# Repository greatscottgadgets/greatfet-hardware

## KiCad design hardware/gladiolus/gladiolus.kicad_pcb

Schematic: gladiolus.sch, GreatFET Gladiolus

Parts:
C1, C4: C; 0603
C2, C10, C26: 15pF; 0402; Part Number GRM1555C1H150GA01D
C3, C5, C6, C7, C11, C12, C13, C17, C18, C19, C20, C21, C22, C23, C24, C25, C27: 100nF; 0603; Part Number GRM188R71C104KA01D
C8: 10uF; 0805; Part Number GRM21BR61A106KE19L
C9: 100pF; 0402; Part Number GRM1555C1H101GA01D
C14: 130pF; 0402; Part Number GRM1555C1H131GA01D
C15: 82pF; 0402; Part Number GRM1555C1H820GA01D
C16: 24pF; 0402; Part Number GRM1555C1H240GA01D
D1: PHOTODIODE; LED-3MM; Part Number PD204-6B
D2: PHOTODIODE; VBPW34FASR; Part Number VBPW34FASR
D3: LED; LED-5MM; Part Number TSHF5210
FB1: FILTER; 0805; Part Number BLM21PG221SN1D
J1: NEIGHBOR1; HEADER-2x20; Part Number SSQ-120-23-G-D
J2: NEIGHBOR2; HEADER-2x20; Part Number SSQ-120-23-G-D
J7: BONUS_ROW; HEADER-1x20; Part Number SSQ-120-23-G-S
L1, L2, L5, L6, L7, L8: 2.2uH; 0402; Part Number MLF1005G2R2JT000
L3, L4: 1.5uH; 0402; Part Number MLF1005G1R5KT000
L9, L10: 1uH; 0402; Part Number MLF1005G1R0JT000
MH1, MH2, MH3, MH4: MOUNTING_HOLE; HOLE126MIL-COPPER
P1: CONN_01X05; HEADER-1x5; Part Number PPTC051LFBN-RC
Q1: Q_NPN_BEC; SOT23-3; Part Number BSV52
R1, R2, R3, R4, R9, R19, R20, R21, R22, R23, R26, R29, R31, R38, R39, R40, R41, R42, R43, R44, R45, R67, R72, R74: 0; 0603; Part Number RC0603JR-070RL
R5, R11, R12, R13, R14, R37, R56, R65, R68: R; 0603
R6: 100k; 0402; Part Number RC0402FR-07100KL
R7: 3.24k; 0603; Part Number RC0603FR-073K24L
R8: 1.74k; 0603; Part Number RC0603FR-071K74L
R10, R27, R36, R55, R58, R59, R60, R61, R62, R63: 10k; 0603; Part Number ERJ-3GEYJ103V
R15, R16, R32, R33: 0; 0402; Part Number RC0402JR-070RL
R17, R18, R34, R35: R; 0402
R24, R25, R73: 1k; 0603; Part Number RC0603JR-071KL
R28, R46, R47, R48, R49, R50, R51, R52, R53, R54: 39; 0603; Part Number RC0603JR-0739RL
R30: 75; 0603; Part Number RC0603FR-0775RL
R57: 20k; 0603; Part Number RC0603JR-0720KL
R64, R66, R69: 249; 0603; Part Number 311-249HR
R70: 1.80k; 0603; Part Number RC0603FR-071K8L
R71: 953; 0603; Part Number RC0603FR-07953RL
R75: 12k; 0603; Part Number RC0603JR-0712KL
RV1, RV2, RV3: POT; 3306F; Part Number 3306F-1-103
U1: THS4520RGT; QFN16-3; Part Number THS4520RGT
U2: AD8330ARQZ; TSSOP16; Part Number AD8330ARQZ
U3: AD9283; SSOP20; Part Number AD9283BRSZ-50
U4: AD9704; QFN32-5; Part Number AD9704BCPZ
U5: LMH6643; VSSOP8; Part Number LMH6643MM

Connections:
/ADC0_0: J2.5, R21.2
/ADC0_2: J7.5
/ADC0_5: J7.4
/ADCCLK: R37.1, R46.1, U3.10 (ENCODE)
/CLK0: J1.11
/CLK2: J2.12
/D0: R38.2, U3.20 (D0)
/D1: R39.2, U3.19 (D1)
/D2: R40.2, U3.18 (D2)
/D3: R41.2, U3.17 (D3)
/D4: R42.2, U3.14 (D4)
/D5: R43.2, U3.13 (D5)
/D6: R44.2, U3.12 (D6)
/D7: R45.2, U3.11 (D7)
/DACCLK: R54.1, R56.1, U4.12
/I2C0_SCL: J2.40
/I2C0_SDA: J2.39
/P0_0: J1.4, R38.1
/P0_1: J1.6, R39.1
/P1_0: J1.7, R45.1
/P1_1: J1.10
/P1_2: J1.12
/P1_3: J1.40
/P1_4: J1.39
/P1_5: J1.13, R24.2
/P1_6: J1.16, R54.2
/P1_7: J1.15, R53.2
/P1_8: J1.18, R52.2
/P1_9: J1.17, R51.2
/P1_10: J1.20, R50.2
/P1_11: J1.22, R49.2
/P1_12: J1.21, R48.2
/P1_13: J1.26, R47.2
/P1_14: J1.25, R28.2
/P1_15: J1.28, R40.1
/P1_16: J1.30, R41.1
/P1_17: J1.32
/P1_18: J1.31
/P1_19: J1.38
/P1_20: J1.37
/P2_0: J1.35
/P2_1: J2.35
/P2_2: J2.33, R44.1
/P2_3: J2.20, R36.1, U3.1 (PWRDWN)
/P2_4: J2.19
/P2_5: J2.18, R9.2, R10.2, R19.1
/P2_6: J2.15
/P2_7: J2.14
/P2_8: J2.13
/P2_9: J7.6
/P2_10: J7.14
/P2_11: J7.13
/P2_12: J7.7
/P2_13: J7.8
/P3_0: J2.26
/P3_1: J2.24
/P3_2: J2.22
/P3_3: J2.32
/P3_4: J2.28
/P3_5: J2.37
/P3_6: J2.38
/P3_7: J2.30
/P4_0: J2.4
/P4_2: J2.8
/P4_3: J2.9, R29.2
/P4_4: J2.7, R22.2
/P4_5: J2.6
/P4_6: J2.10
/P4_7: J2.11
/P4_8: J2.3, R26.2
/P4_9: J1.3
/P4_10: J1.5
/P5_0: J1.8, R55.2, U4.25
/P5_1: J1.9
/P5_2: J1.14, R58.2, R59.1, U4.15
/P5_3: J1.19, R60.2, R61.1, U4.16
/P5_4: J1.24
/P5_5: J1.23, R62.2, R63.1, U4.17
/P5_6: J1.27, R25.2
/P5_7: J1.29
/P6_0: J1.36
/P6_1: J7.18
/P6_2: J7.17
/P6_3: J2.36, R42.1
/P6_4: J7.2
/P6_5: J7.3
/P6_6: J2.34, R43.1
/P6_7: J2.31
/P6_8: J2.29
/P6_9: J7.16
/P6_10: J7.15
/P7_0: J2.27
/P7_1: J2.25
/P7_2: J2.23
/P7_7: J2.16
/P9_5: J1.33
/P9_6: J1.34, R46.2
/PF_4: J2.21
/RESET: J7.11
/RTC_ALARM: J7.9
/RXIN: C2.2, D1.2 (A), D2.2 (A), P1.5, R5.1, R6.2, U1.11 (VIN+)
/TXOUT: D3.1 (K), P1.1, Q1.3 (C)
/VBAT: J7.12
/VBUS: J2.2, R3.2
/WAKEUP0: J2.17
GND: C1.2, C3.2, C5.2, C6.2, C7.2, C8.2, C11.2, C12.2, C13.2, C17.1, C18.1, C19.1, C20.1, C21.2, C22.2, C23.2, C24.1, C25.2, C27.2, J1.1, J2.1, J7.1, J7.10, J7.19, MH1.1, MH2.1, MH3.1, MH4.1, P1.2, P1.4, R4.2, R8.1, R10.1, R14.2, R17.1, R18.2, R20.2, R27.2, R30.2, R34.1, R35.2, R37.2, R56.2, R57.1, R59.2, R61.2, R63.2, R64.2, R66.2, R70.2, RV1.1, RV2.1, RV3.1, U1.0 (GND), U1.13 (VS-), U1.14 (VS-), U1.15 (VS-), U1.16 (VS-), U2.8 (CMGN), U2.9 (COMM), U2.11 (CMOP), U3.4 (GND), U3.9 (GND), U3.16 (GND), U4.0, U4.10, U4.14, U4.19, U4.22, U4.26, U5.4
unnamed: C1.1, D1.1 (K), D2.1 (K), R1.2, R2.1, R3.1, R4.1
unnamed: C2.1, L1.2, R6.1, U1.10 (VOUT-)
unnamed: C3.1, C4.2, R1.1, R7.1, R8.2, R11.1, R12.1, RV1.2, U1.2 (VIN-)
unnamed: C4.1, L2.2, R11.2, U1.3 (VOUT+)
unnamed: C5.1, R5.2, U1.9 (CM)
unnamed: C7.1, R12.2, R13.2, R14.1, U1.4 (CM)
unnamed: C9.1, L1.1, L3.2
unnamed: C9.2, L2.1, L4.2
unnamed: C10.1, L3.1, R15.1
unnamed: C10.2, L4.1, R16.1
unnamed: C13.1, R31.1, U2.15 (CNTR)
unnamed: C14.1, L5.1, L7.2
unnamed: C14.2, L6.1, L8.2
unnamed: C15.1, L7.1, L9.2
unnamed: C15.2, L8.1, L10.2
unnamed: C16.1, L9.1, R32.1
unnamed: C16.2, L10.1, R33.1
unnamed: C18.2, R31.2, U3.2 (VREFOUT), U3.3 (VREFIN)
unnamed: C24.2, R67.1, R68.2, U4.23
unnamed: C25.1, R24.1, R25.1, R27.1, R65.2, R67.2, U5.3
unnamed: C26.1, R68.1, R69.1, R70.1, R71.1, U5.2
unnamed: C26.2, R71.2, R72.1, U5.1
unnamed: FB1.2, J1.2
unnamed: L5.2, U2.13 (OPHI)
unnamed: L6.2, U2.12 (OPLO)
unnamed: Q1.1 (B), R73.1
unnamed: Q1.2 (E), R30.1, R74.2
unnamed: R9.1, U1.12 (!PD)
unnamed: R15.2, R17.2, U2.4 (INHI)
unnamed: R16.2, R18.1, U2.5 (INLO)
unnamed: R19.2, U2.2 (ENBL)
unnamed: R20.1, U2.1 (OFST)
unnamed: R21.1, R22.1, RV2.2, U2.7 (VDBS)
unnamed: R23.1, R26.1, U2.6 (MODE)
unnamed: R28.1, U4.27
unnamed: R29.1, RV3.2, U2.10 (VMAG)
unnamed: R32.2, R34.2, U3.6 (AIN-)
unnamed: R33.2, R35.1, U3.7 (AIN+)
unnamed: R47.1, U4.28
unnamed: R48.1, U4.29
unnamed: R49.1, U4.30
unnamed: R50.1, U4.31
unnamed: R51.1, U4.32
unnamed: R52.1, U4.1
unnamed: R53.1, U4.2
unnamed: R57.2, U4.24
unnamed: R72.2, U5.5
unnamed: R73.2, U5.7
unnamed: R74.1, U5.6
unnamed: R75.1, RV2.3
VCC: C6.1, C8.1, C11.1, C12.1, C17.2, C19.2, C20.2, C21.1, C22.1, C23.1, C27.1, D3.2 (A), FB1.1, P1.3, R2.2, R7.2, R13.1, R23.2, R36.2, R55.1, R58.1, R60.1, R62.1, R75.2, RV1.3, RV3.3, U1.5 (VS+), U1.6 (VS+), U1.7 (VS+), U1.8 (VS+), U2.3 (VPSI), U2.14 (VPSO), U2.16 (VPOS), U3.5 (VD), U3.8 (VD), U3.15 (VDD), U4.3, U4.11, U4.18, U5.8

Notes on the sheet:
MISO
MOSI
SCK
SSEL
ISP
DFU
BOOT
10 MHz LPF
SGPIO0
SGPIO1
SGPIO2
SGPIO3
SGPIO4
SGPIO5
SGPIO6
SGPIO7
SGPIO8
P1 blocks direct light from TX to RX
GPIO1[0]
GPIO1[1]
GPIO1[2]
GPIO1[3]
GPIO1[4]
GPIO1[5]
GPIO1[6]
GPIO1[7]
GPIO1[9]
Default configuration: pin mode unsigned binary single-ended clock
GPIO1[8]
GPIO2[15]
GPIO2[12]
GPIO2[14]
GPIO2[11]
GPIO2[9]

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
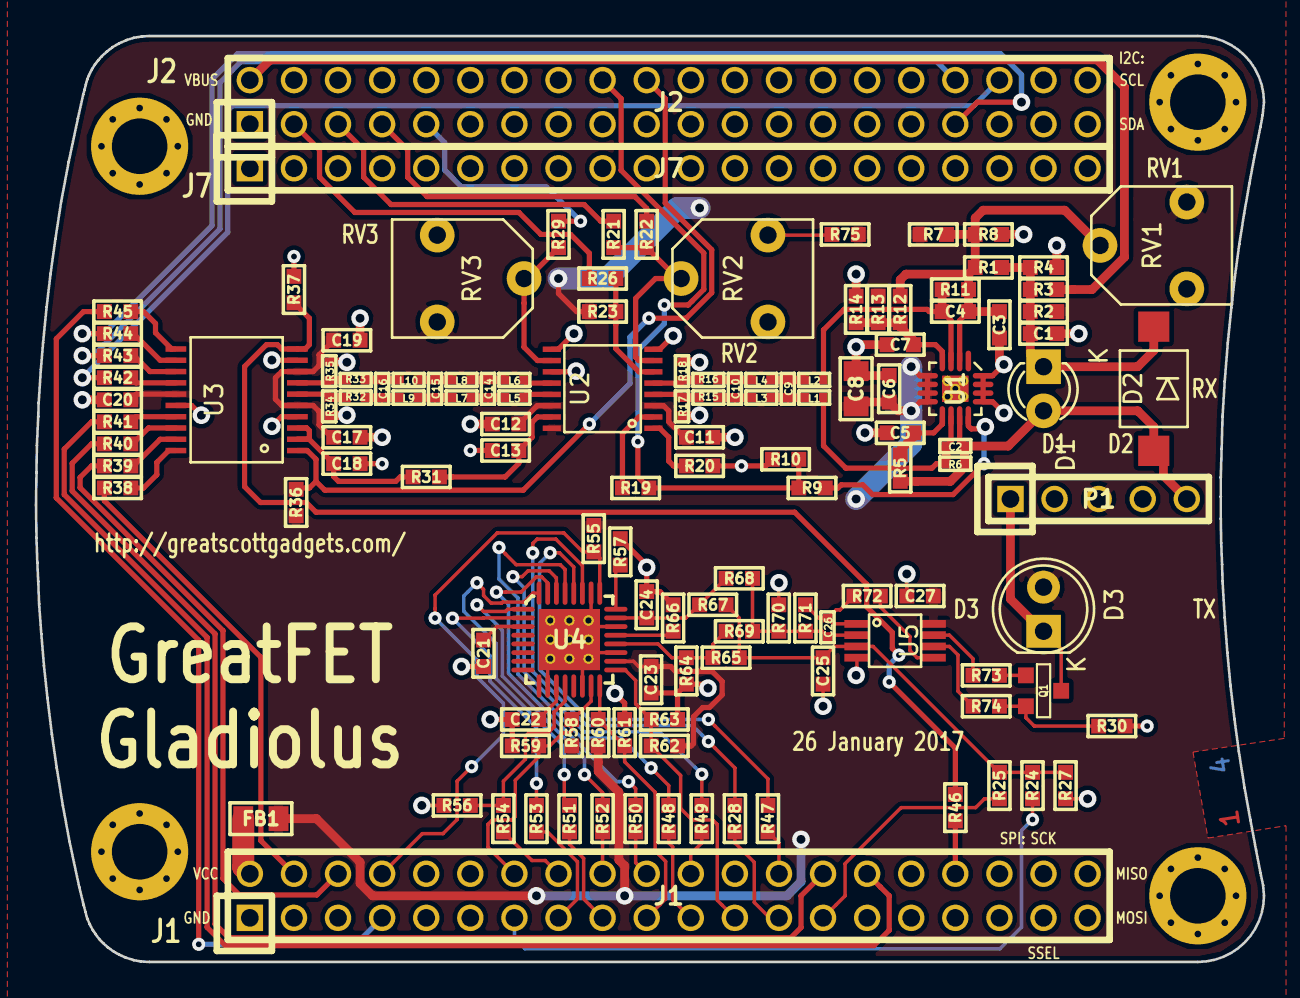
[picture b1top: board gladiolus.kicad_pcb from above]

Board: 4 copper layers, 70.7 x 53.3 mm, 133 parts (0 on the bottom side), 97 nets.

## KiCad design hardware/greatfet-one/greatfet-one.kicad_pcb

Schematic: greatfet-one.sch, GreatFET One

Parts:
C1, C2, C5, C6, C8, C9: 18pF; 0603; Part Number GRM1885C1H180JA01D
C3, C10: 1uF; 0603; Part Number LMK107B7105KA-T
C4, C11: 10uF; 0805; Part Number GRM21BR61A106KE19L
C7, C12, C13, C14, C15, C16, C17, C18, C19, C20, C21, C22, C23, C24, C25: 100nF; 0603; Part Number GRM188R71C104KA01D
D1: LED1; 0603D; Part Number SML-LX0603GW-TR
D2: LED2; 0603D; Part Number SML-LX0603YW-TR
D3: LED3; 0603D; Part Number SML-LX0603GW-TR
D4: LED4; 0603D; Part Number SML-LX0603YW-TR
D5: VBUS_DIODE; SOD128; Part Number PMEG3050EP,115
FB1, FB2, FB3: FILTER; 0805; Part Number BLM21PG221SN1D
J1: NEIGHBOR1; HEADER-2x20; Part Number SSW-120-21-L-D
J2: NEIGHBOR2; HEADER-2x20; Part Number SSW-120-21-L-D
J3, J4: USB-MICRO-B-SHIELDED; USB-MICROB-FCI-10103592-LONGPADS; Part Number 10103592-0001LF
J5: JTAG; 50MIL-HEADER-2x5-TH
J6: POWER; HEADER-SMT-2x4
J7: BONUS_ROW; HEADER-1x20; Part Number TSW-120-07-L-S
MH1, MH2, MH3, MH4: MOUNTING_HOLE; HOLE126MIL-COPPER
R1, R2, R3, R4: 330; 0603; Part Number RMCF0603JT330R
R5, R6, R7, R8, R9, R10, R11, R12, R14, R15, R16, R21, R24, R25: 10k; 0603; Part Number ERJ-3GEYJ103V
R13: 12.0k; 0603; Part Number RMCF0603FT12K0
R17, R18: 1.8k; 0603; Part Number RMCF0603JT1K80
R19, R20: 33.0; 0603; Part Number MCR03ERTF33R0
R22, R26: 18k; 0603; Part Number RC0603JR-0718KL
R23: 43.2k; 0603; Part Number RC0603FR-0743K2L
R27, R28, R29, R30: 15k; 0603; Part Number RC0603JR-0715KL
SW1: DFU; SWITCH-PTS840-P; Part Number PTS840 PM SMTR LFS
SW2: RESET; SWITCH-PTS840-P; Part Number PTS840 PM SMTR LFS
TP1: DBGEN; TESTPOINT-50MIL
TP2: TRST; TESTPOINT-50MIL
TP3: LED1; TESTPOINT-50MIL
TP4: LED2; TESTPOINT-50MIL
TP5: LED3; TESTPOINT-50MIL
TP6: LED4; TESTPOINT-50MIL
TP7: USB1_VBUS; TESTPOINT-50MIL
TP8: USB1_SENSE; TESTPOINT-50MIL
TP9: SPIFI_CS; TESTPOINT-50MIL
TP10: USB1_EN; TESTPOINT-50MIL
TP11: USB1_FAULT; TESTPOINT-50MIL
TP12: USB1_ID; TESTPOINT-50MIL
TP13: USB0_ID; TESTPOINT-50MIL
TP14: USB0_VBUS; TESTPOINT-50MIL
TP15: USB0_SENSE; TESTPOINT-50MIL
TP16: TMS; TESTPOINT-50MIL
TP17: TCK; TESTPOINT-50MIL
TP18: TDO; TESTPOINT-50MIL
TP19: TDI; TESTPOINT-50MIL
U1: LPC4330FBD144; LQFP144; Part Number LPC4330FBD144,551
U2: W25Q16DV; SOIC8-208; Part Number W25Q16JVSSIQ
U3: AP7333; SOT23-3; Part Number AP7333-33SAG-7
U4: IP4220CZ6; SOT457; Part Number IP4220CZ6,125
U5: AP2553W6-7; SOT457; Part Number AP2553W6-7
W1: VBUS_BYPASS; 0603-JUMPER
X1: MCU_XTAL; XTAL3.2x2.5mm-EXT; Part Number 7V-12.000MAAE-T
X2: RTC_XTAL; XTAL-AB26TRQ; Part Number AB26TRQ-32.768KHZ-T

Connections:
+5V: C4.1, C10.1, D5.1 (K), J2.2, J6.5, J6.6, U3.1 (IN), U5.1 (VIN), W1.1
/ADC0_0: J2.5, U1.6 (ADC0_0/ADC1_0/DAC)
/ADC0_2: J7.5, U1.143 (ADC0_2/ADC1_2)
/ADC0_5: J7.4, U1.144 (ADC0_5/ADC1_5)
/CLK0: J1.11, U1.45 (CLK0)
/CLK2: J2.12, U1.99 (CLK2)
/DBGEN: R10.2, TP1.1, U1.28 (DBGEN)
/I2C0_SCL: J2.40, R18.2, U1.92 (I2C0_SCL)
/I2C0_SDA: J2.39, R17.2, U1.93 (I2C0_SDA)
/LED1: D1.1 (K), TP3.1, U1.134 (P7_6)
/LED2: D2.1 (K), TP4.1, U1.3 (P4_1)
/LED3: D3.1 (K), TP5.1, U1.133 (P7_5)
/LED4: D4.1 (K), TP6.1, U1.132 (P7_4)
/P0_0: J1.4, U1.32 (P0_0)
/P0_1: J1.6, U1.34 (P0_1)
/P1_0: J1.7, U1.38 (P1_0)
/P1_1: J1.10, R9.2, U1.42 (P1_1)
/P1_2: J1.12, R8.1, U1.43 (P1_2)
/P1_3: J1.40, U1.44 (P1_3)
/P1_4: J1.39, U1.47 (P1_4)
/P1_5: J1.13, U1.48 (P1_5)
/P1_6: J1.16, U1.49 (P1_6)
/P1_7: J1.15, U1.50 (P1_7)
/P1_8: J1.18, U1.51 (P1_8)
/P1_9: J1.17, U1.52 (P1_9)
/P1_10: J1.20, U1.53 (P1_10)
/P1_11: J1.22, U1.55 (P1_11)
/P1_12: J1.21, U1.56 (P1_12)
/P1_13: J1.26, U1.60 (P1_13)
/P1_14: J1.25, U1.61 (P1_14)
/P1_15: J1.28, U1.62 (P1_15)
/P1_16: J1.30, U1.64 (P1_16)
/P1_17: J1.32, U1.66 (P1_17)
/P1_18: J1.31, U1.67 (P1_18)
/P1_19: J1.38, U1.68 (P1_19)
/P1_20: J1.37, U1.70 (P1_20)
/P2_0: J1.35, U1.75 (P2_0)
/P2_1: J2.35, U1.81 (P2_1)
/P2_2: J2.33, U1.84 (P2_2)
/P2_3: J2.20, U1.87 (P2_3)
/P2_4: J2.19, U1.88 (P2_4)
/P2_5: J2.18, U1.91 (P2_5)
/P2_6: J2.15, U1.95 (P2_6)
/P2_7: J2.14, R15.2, U1.96 (P2_7)
/P2_8: J2.13, R6.1, SW1.1, U1.98 (P2_8)
/P2_9: J7.6, R7.1, U1.102 (P2_9)
/P2_10: J7.14, U1.104 (P2_10)
/P2_11: J7.13, U1.105 (P2_11)
/P2_12: J7.7, U1.106 (P2_12)
/P2_13: J7.8, U1.108 (P2_13)
/P3_0: J2.26, U1.112 (P3_0)
/P3_1: J2.24, U1.114 (P3_1)
/P3_2: J2.22, U1.116 (P3_2)
/P3_3: J2.32, U1.118 (P3_3), U2.6 (CLK)
/P3_4: J2.28, U1.119 (P3_4), U2.7 (HOLD)
/P3_5: J2.37, U1.121 (P3_5), U2.3 (WP)
/P3_6: J2.38, U1.122 (P3_6), U2.2 (DO)
/P3_7: J2.30, U1.123 (P3_7), U2.5 (DI)
/P4_0: J2.4, U1.1 (P4_0)
/P4_2: J2.8, U1.8 (P4_2)
/P4_3: J2.9, U1.7 (P4_3)
/P4_4: J2.7, U1.9 (P4_4)
/P4_5: J2.6, U1.10 (P4_5)
/P4_6: J2.10, U1.11 (P4_6)
/P4_7: J2.11, U1.14 (P4_7)
/P4_8: J2.3, U1.15 (P4_8)
/P4_9: J1.3, U1.33 (P4_9)
/P4_10: J1.5, U1.35 (P4_10)
/P5_0: J1.8, U1.37 (P5_0)
/P5_1: J1.9, U1.39 (P5_1)
/P5_2: J1.14, U1.46 (P5_2)
/P5_3: J1.19, U1.54 (P5_3)
/P5_4: J1.24, U1.57 (P5_4)
/P5_5: J1.23, U1.58 (P5_5)
/P5_6: J1.27, U1.63 (P5_6)
/P5_7: J1.29, U1.65 (P5_7)
/P6_0: J1.36, U1.73 (P6_0)
/P6_1: J7.18, U1.74 (P6_1)
/P6_2: J7.17, U1.78 (P6_2)
/P6_3: J2.36, U1.79 (P6_3)
/P6_4: J7.2, U1.80 (P6_4)
/P6_5: J7.3, U1.82 (P6_5)
/P6_6: J2.34, U1.83 (P6_6)
/P6_7: J2.31, U1.85 (P6_7)
/P6_8: J2.29, U1.86 (P6_8)
/P6_9: J7.16, U1.97 (P6_9)
/P6_10: J7.15, U1.100 (P6_10)
/P7_0: J2.27, U1.110 (P7_0)
/P7_1: J2.25, U1.113 (P7_1)
/P7_2: J2.23, U1.115 (P7_2)
/P7_7: J2.16, U1.140 (P7_7)
/P9_5: J1.33, U1.69 (P9_5)
/P9_6: J1.34, U1.72 (P9_6)
/PF_4: J2.21, U1.120 (PF_4)
/RESET: J5.10, J7.11, R5.2, SW2.1, U1.128 (RESET)
/RTCX1: C2.1, U1.125 (RTCX1), X2.2
/RTCX2: C1.1, U1.126 (RTCX2), X2.1
/RTC_ALARM: J7.9, U1.129 (RTC_ALARM)
/SPIFI_CS: TP9.1, U1.124 (P3_8), U2.1 (CS)
/TCK: J5.4, R11.2, TP17.1, U1.27 (TCK/SWDCLK)
/TDI: J5.8, TP19.1, U1.26 (TDI)
/TDO: J5.6, R12.2, TP18.1, U1.31 (TDO/SWO)
/TMS: J5.2, TP16.1, U1.30 (TMS/SWDIO)
/TRST: TP2.1, U1.29 (TRST)
/USB0_D+: J3.3 (D+), R28.1, U1.18 (USB0_DP), U4.1 (ESD1)
/USB0_D-: J3.2 (D-), R27.1, U1.20 (USB0_DM), U4.6 (ESD4)
/USB0_ID: J3.4 (ID), TP13.1, U1.22 (USB0_ID), U4.3 (ESD2)
/USB0_SENSE: R25.2, R26.2, TP15.1, U1.21 (USB0_VBUS)
/USB0_SHIELD: FB2.2, J3.0 (SHIELD)
/USB0_VBUS: FB1.1, J3.1 (VBUS), TP14.1, U4.5 (VP)
/USB1_D+: C9.1, R20.2, R30.1, U1.89 (USB1_DP)
/USB1_D-: C8.1, R19.2, R29.1, U1.90 (USB1_DM)
/USB1_EN: R16.2, TP10.1, U1.103 (P6_12), U5.3 (EN)
/USB1_FAULT: R24.1, TP11.1, U1.117 (P7_3), U5.4 (FAULT)
/USB1_ID: J4.4 (ID), TP12.1
/USB1_SENSE: R21.2, R22.2, TP8.1, U1.101 (P6_11)
/USB1_SHIELD: FB3.1, J4.0 (SHIELD)
/USB1_VBUS: C11.1, J4.1 (VBUS), J6.7, J6.8, R21.1, TP7.1, U5.6 (VOUT)
/VBAT: J7.12, U1.127 (VBAT)
/WAKEUP0: J2.17, R14.2, U1.130 (WAKEUP0)
GND: C1.2, C2.2, C3.2, C4.2, C5.2, C6.2, C7.2, C8.2, C9.2, C10.2, C11.2, C12.2, C13.2, C14.2, C15.2, C16.2, C17.2, C18.2, C19.2, C20.2, C21.2, C22.2, C23.2, C24.2, C25.2, FB2.1, FB3.2, J1.1, J2.1, J3.5 (GND), J4.5 (GND), J5.3, J5.5, J5.9, J6.1, J6.2, J7.1, J7.10, J7.19, MH1.1, MH2.1, MH3.1, MH4.1, R6.2, R7.2, R8.2, R13.2, R16.1, R22.1, R23.1, R26.1, R27.2, R28.2, R29.2, R30.2, SW2.2, U1.4 (VSSIO), U1.19 (USB0_VSSA_TERM), U1.23 (USB0_VSSA_REF), U1.40 (VSSIO), U1.76 (VSSIO), U1.109 (VSSIO), U1.135 (VSSA), U2.4 (GND), U3.3 (GND), U4.2 (GND), U5.2 (GND), X1.2, X1.4
unnamed: C5.1, U1.12 (XTAL1), X1.1
unnamed: C6.1, U1.13 (XTAL2), X1.3
unnamed: D1.2 (A), R1.2
unnamed: D2.2 (A), R2.2
unnamed: D3.2 (A), R3.2
unnamed: D4.2 (A), R4.2
unnamed: D5.2 (A), FB1.2, R25.1, W1.2
unnamed: J4.2 (D-), R19.1
unnamed: J4.3 (D+), R20.1
unnamed: R13.1, U1.24 (USB0_RREF)
unnamed: R23.2, U5.5 (ILIM)
VCC: C3.1, C7.1, C12.1, C13.1, C14.1, C15.1, C16.1, C17.1, C18.1, C19.1, C20.1, C21.1, C22.1, C23.1, C24.1, C25.1, J1.2, J5.1, J6.3, J6.4, J7.20, R1.1, R2.1, R3.1, R4.1, R5.1, R9.1, R10.1, R11.1, R12.1, R14.1, R15.1, R17.1, R18.1, R24.2, SW1.2, U1.5 (VDDIO), U1.16 (USB0_VDDA3V3_DRIVER), U1.17 (USB0_VDDA3V3), U1.25 (VDDREG), U1.36 (VDDIO), U1.41 (VDDIO), U1.59 (VDDREG), U1.71 (VDDIO), U1.77 (VDDIO), U1.94 (VDDREG), U1.107 (VDDIO), U1.111 (VDDIO), U1.131 (VDDREG), U1.137 (VDDA), U1.141 (VDDIO), U2.8 (VCC), U3.2 (OUT)

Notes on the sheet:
MISO
MOSI
SCK
SSEL
ISP
DFU
BOOT
bonus row is optional for neighbors
boot selection
test points
Default boot configuration is SPIFI. Hold SW1 through reset to boot to USB0 (DFU) mode.
Cortex Debug Connector (10 pin 50 mil)
VCC: 3.3 V +/- 2% Maximum current: 300 mA
USB0_VBUS must be between 4.4 V and 5.25 V but may be disconnected if +5V is supplied via J2.
+5V may have an actual voltage from 3.6 V to 5.25 V. J2 pin 2 may be used as a power input, supplying +5V. If so, be prepared for USB0_VBUS (or another neighbor supplying +5V) to appear, possibly reversing the current on J2 pin 2.
+5V should be between 4.75 V and 5.25 V for operation of USB1 in host mode.

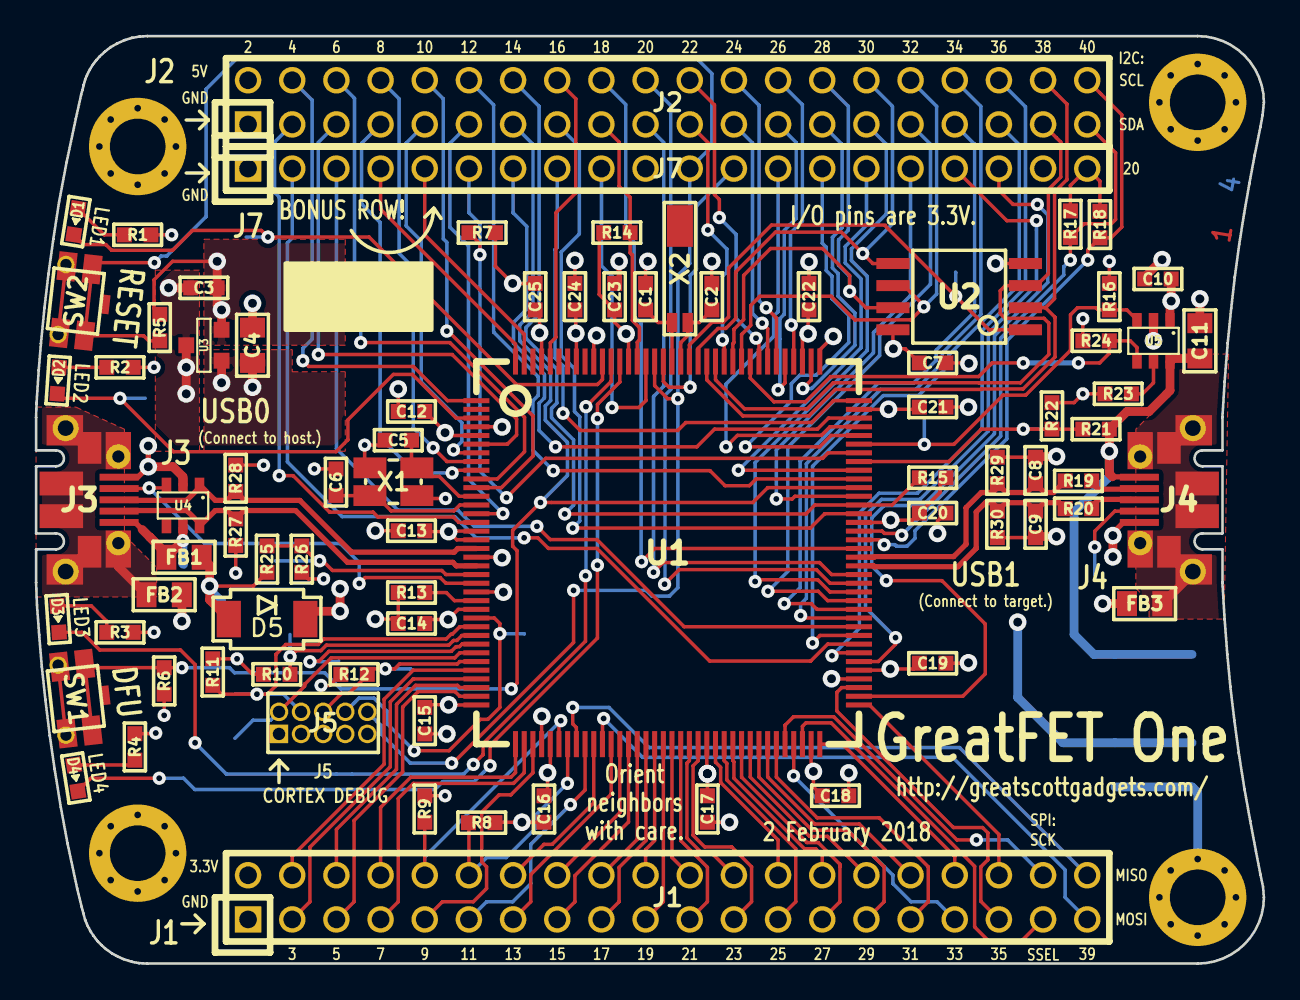
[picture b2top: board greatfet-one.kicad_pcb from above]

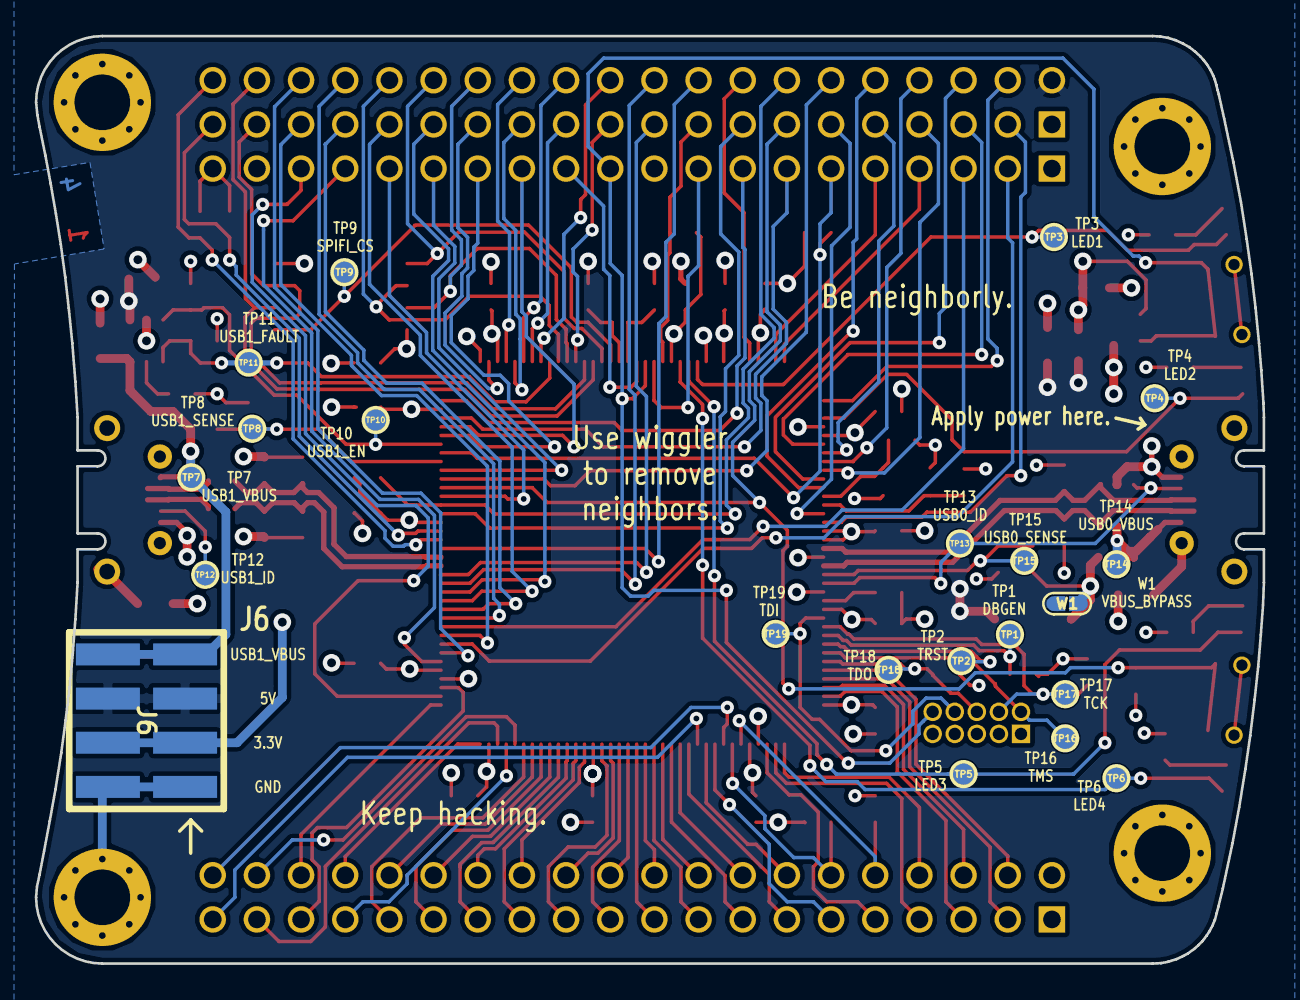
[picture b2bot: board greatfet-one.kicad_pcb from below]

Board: 4 copper layers, 70.6 x 53.3 mm, 103 parts (21 on the bottom side), 133 nets.

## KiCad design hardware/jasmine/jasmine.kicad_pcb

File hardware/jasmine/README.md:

Litium Polymer Battery Charging Neighbor

When operating a GreatFET under LiPo power from Jasmine, the voltage may drop under 3.3VDC.

The 10k resistors on R2 configures the charge current to be 100mA which is the fastest supported charge rate for many LiPo batteries. The charge rate can be reconfigured changing the R2 resistor or adding a resistor to R3.

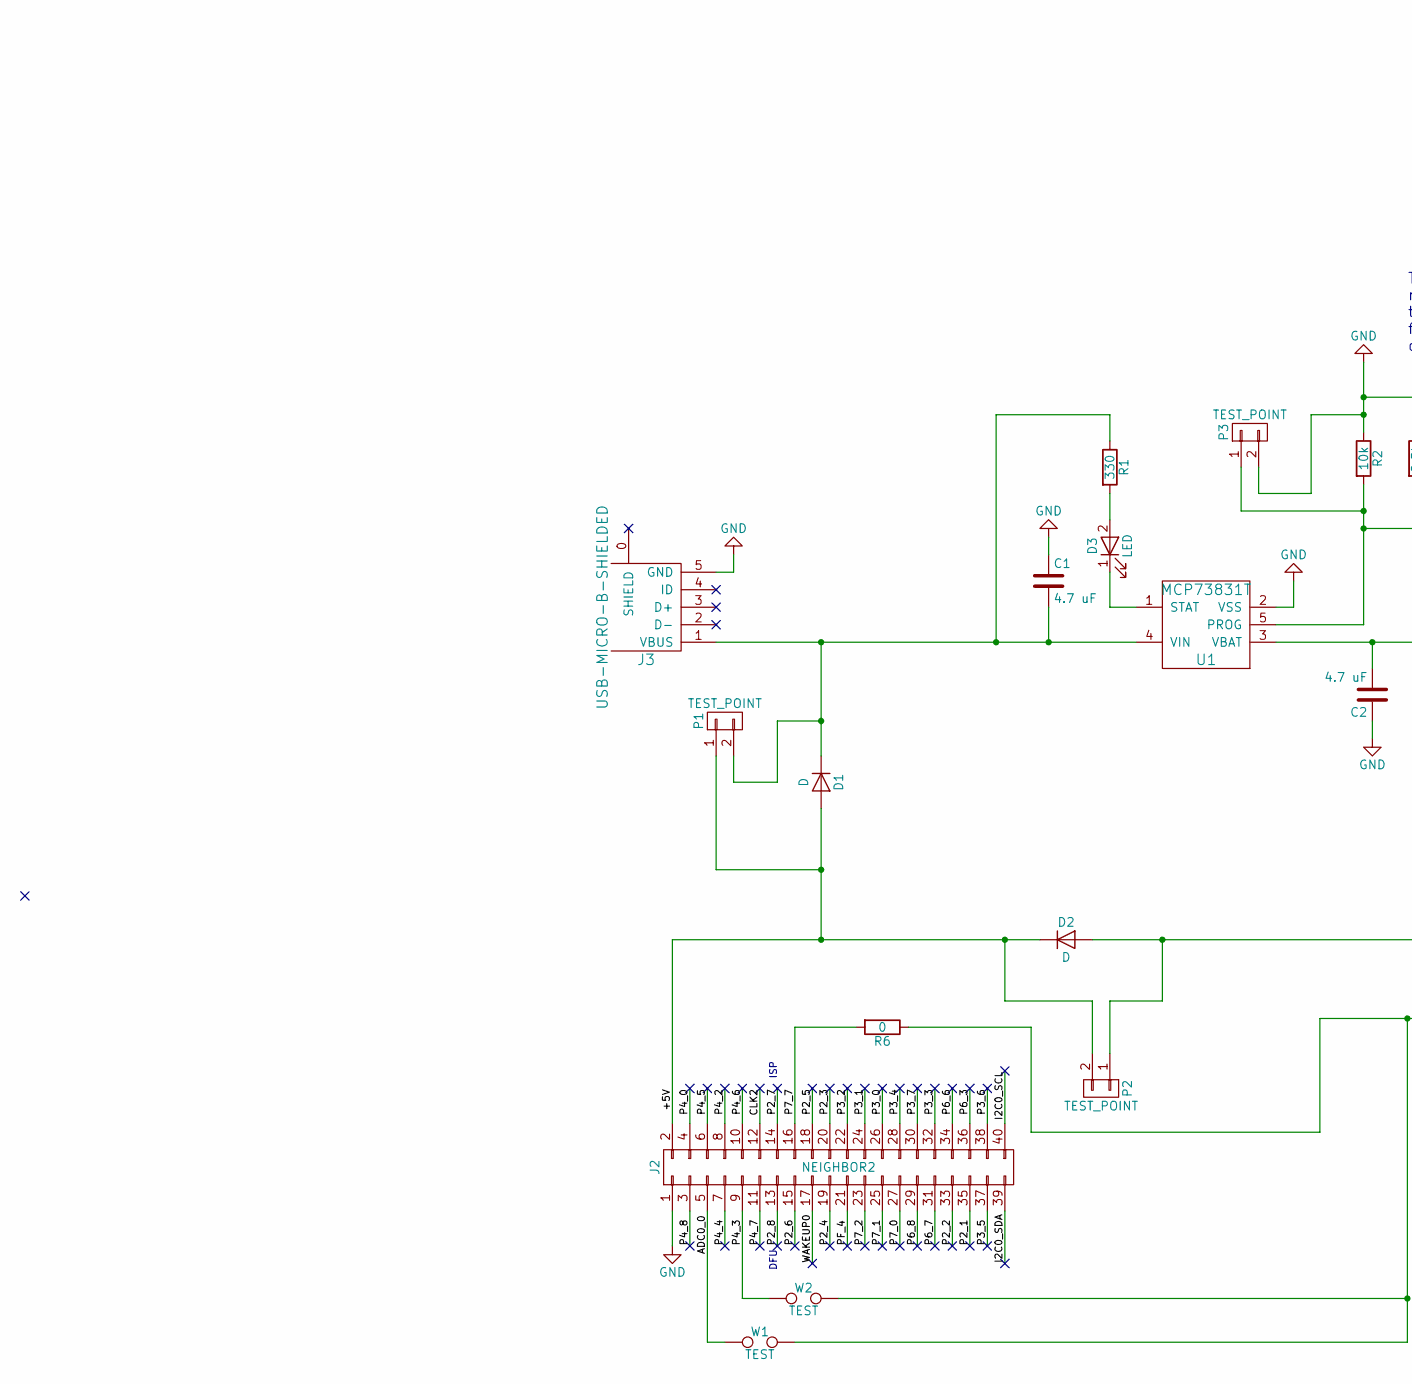
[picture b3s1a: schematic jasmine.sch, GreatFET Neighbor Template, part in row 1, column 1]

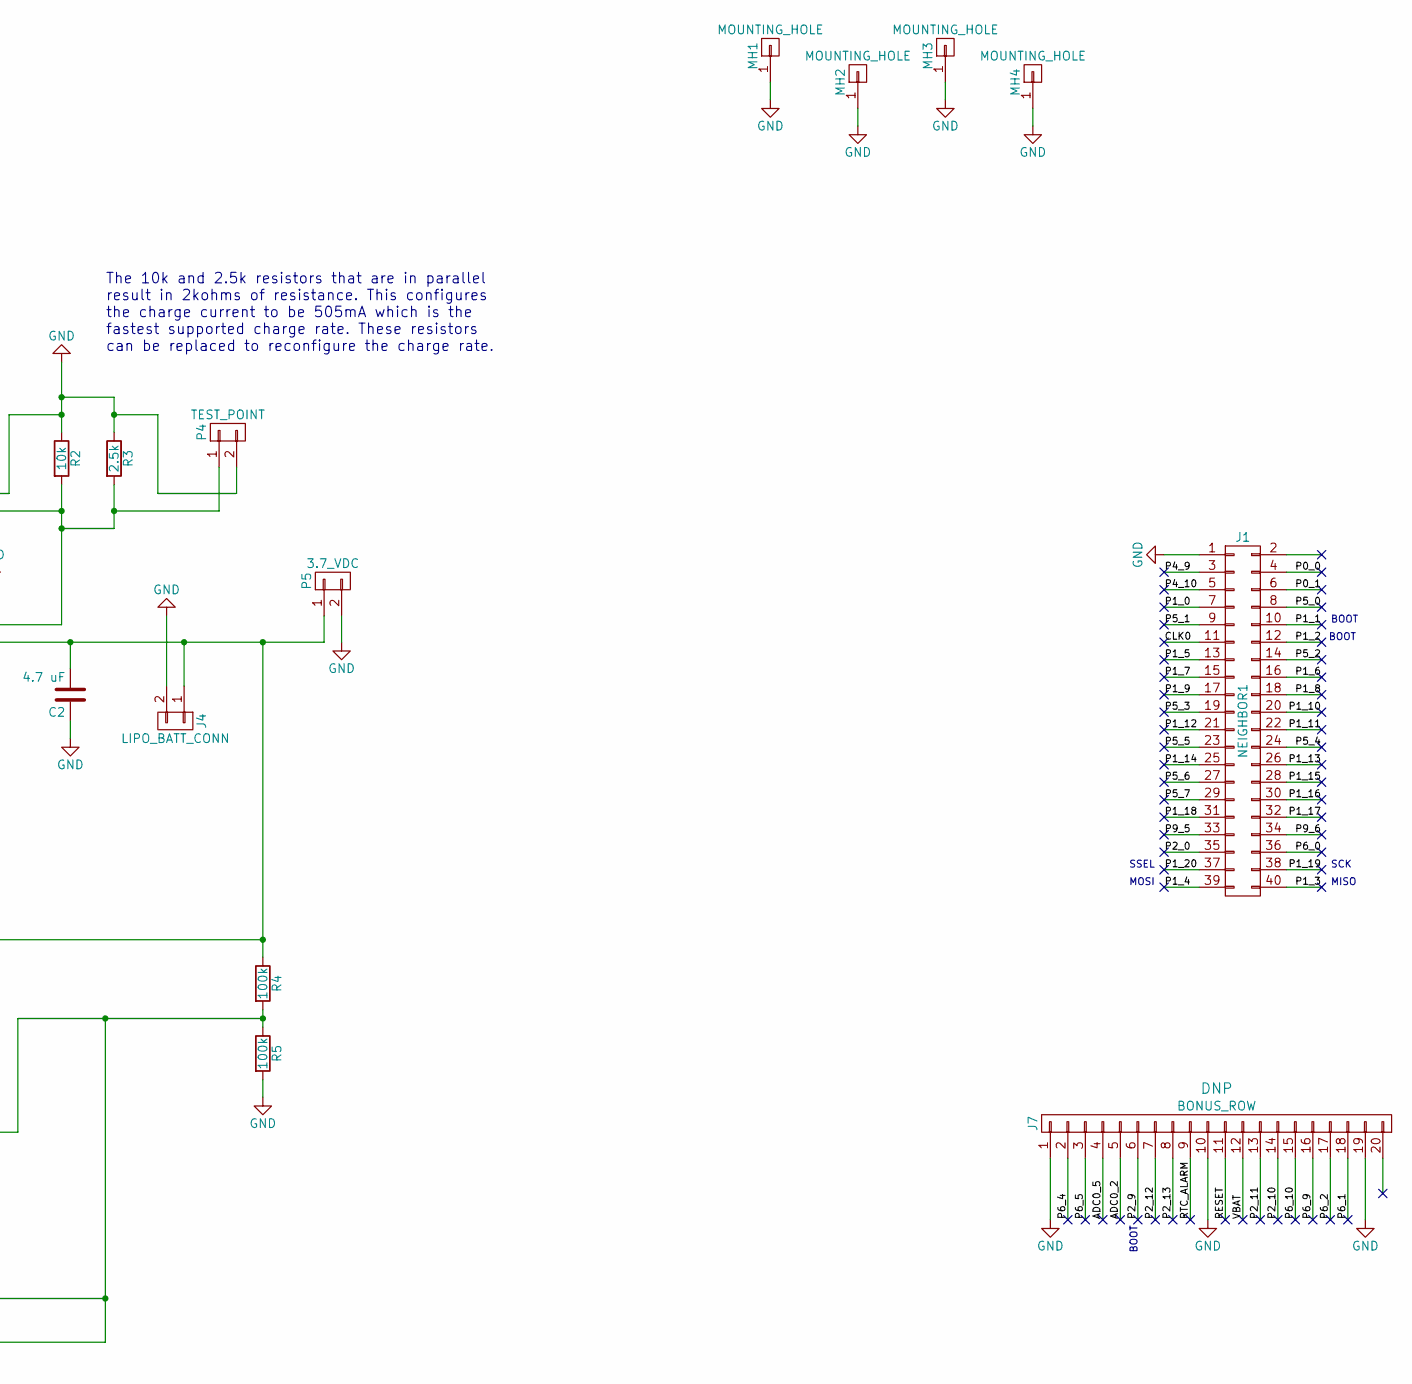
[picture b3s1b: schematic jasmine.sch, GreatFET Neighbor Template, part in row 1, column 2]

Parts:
C1, C2: 4.7 uF; 0603; Part Number GRM188R60J475KE19D
D1, D2: D; SOD128; Part Number PMEG3050EP,115
D3: LED; 0603D; Part Number SML-LX0603GW-TR
J1: NEIGHBOR1; HEADER-2x20; Part Number SSQ-120-23-G-D
J2: NEIGHBOR2; HEADER-2x20; Part Number SSQ-120-23-G-D
J3: USB-MICRO-B-SHIELDED; USB-MICROB-FCI-10103592-LONGPADS; Part Number 10103592-0001LF
J4: LIPO_BATT_CONN; JST_PH_S2B-PH-SM4-TB_02x2.00mm_Angled; Part Number S2B-PH-SM4-TB(LF)(SN)
J7: BONUS_ROW; HEADER-1x20; Part Number SSQ-120-23-G-S
MH1, MH2, MH3, MH4: MOUNTING_HOLE; HOLE126MIL-COPPER
P1, P2, P3, P4: TEST_POINT; HEADER-1x2; Part Number TSW-102-07-F-S
P5: 3.7_VDC; HEADER-1x2
R1: 330; 0603; Part Number RMCF0603JT330R
R2: 10k; 0603; Part Number RC0603FR-0710KL
R3: 2.5k; 0603; Part Number RC0603FR-072K49L
R4, R5: 100k; 0603; Part Number RC0603FR-07100KL
R6: 0; 0603; Part Number RC0603JR-070RL
U1: MCP73831T; SOT-23-5; Part Number MCP73831T-2ACI/OT
W1, W2: TEST; 0603-JUMPER

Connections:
/+5V: D1.2 (A), D2.1 (K), J2.2, P1.1, P2.2
/ADC0_0: J2.5, W1.1
/ADC0_2: J7.5
/ADC0_5: J7.4
/CLK0: J1.11
/CLK2: J2.12
/I2C0_SCL: J2.40
/I2C0_SDA: J2.39
/P0_0: J1.4
/P0_1: J1.6
/P1_0: J1.7
/P1_1: J1.10
/P1_2: J1.12
/P1_3: J1.40
/P1_4: J1.39
/P1_5: J1.13
/P1_6: J1.16
/P1_7: J1.15
/P1_8: J1.18
/P1_9: J1.17
/P1_10: J1.20
/P1_11: J1.22
/P1_12: J1.21
/P1_13: J1.26
/P1_14: J1.25
/P1_15: J1.28
/P1_16: J1.30
/P1_17: J1.32
/P1_18: J1.31
/P1_19: J1.38
/P1_20: J1.37
/P2_0: J1.35
/P2_1: J2.35
/P2_2: J2.33
/P2_3: J2.20
/P2_4: J2.19
/P2_5: J2.18
/P2_6: J2.15
/P2_7: J2.14
/P2_8: J2.13
/P2_9: J7.6
/P2_10: J7.14
/P2_11: J7.13
/P2_12: J7.7
/P2_13: J7.8
/P3_0: J2.26
/P3_1: J2.24
/P3_2: J2.22
/P3_3: J2.32
/P3_4: J2.28
/P3_5: J2.37
/P3_6: J2.38
/P3_7: J2.30
/P4_0: J2.4
/P4_2: J2.8
/P4_3: J2.9, W2.1
/P4_4: J2.7
/P4_5: J2.6
/P4_6: J2.10
/P4_7: J2.11
/P4_8: J2.3
/P4_9: J1.3
/P4_10: J1.5
/P5_0: J1.8
/P5_1: J1.9
/P5_2: J1.14
/P5_3: J1.19
/P5_4: J1.24
/P5_5: J1.23
/P5_6: J1.27
/P5_7: J1.29
/P6_0: J1.36
/P6_1: J7.18
/P6_2: J7.17
/P6_3: J2.36
/P6_4: J7.2
/P6_5: J7.3
/P6_6: J2.34
/P6_7: J2.31
/P6_8: J2.29
/P6_9: J7.16
/P6_10: J7.15
/P7_0: J2.27
/P7_1: J2.25
/P7_2: J2.23
/P7_7: J2.16, R6.2
/P9_5: J1.33
/P9_6: J1.34
/PF_4: J2.21
/RESET: J7.11
/RTC_ALARM: J7.9
/VBAT: J7.12
/WAKEUP0: J2.17
GND: C1.1, C2.1, J1.1, J2.1, J3.5 (GND), J4.2, J7.1, J7.10, J7.19, MH1.1, MH2.1, MH3.1, MH4.1, P3.2, P4.2, P5.2, R2.1, R3.1, R5.2, U1.2 (VSS)
unnamed: C1.2, D1.1 (K), J3.1 (VBUS), P1.2, R1.1, U1.4 (VIN)
unnamed: C2.2, D2.2 (A), J4.1, P2.1, P5.1, R4.1, U1.3 (VBAT)
unnamed: D3.1 (K), U1.1 (STAT)
unnamed: D3.2 (A), R1.2
unnamed: P3.1, P4.1, R2.2, R3.2, U1.5 (PROG)
unnamed: R4.2, R5.1, R6.1, W1.2, W2.2

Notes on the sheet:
MISO
MOSI
SCK
SSEL
ISP
DFU
BOOT
The 10k and 2.5k resistors that are in parallel result in 2kohms of resistance. This configures the charge current to be 505mA which is the fastest supported charge rate. These resistors can be replaced to reconfigure the charge rate.

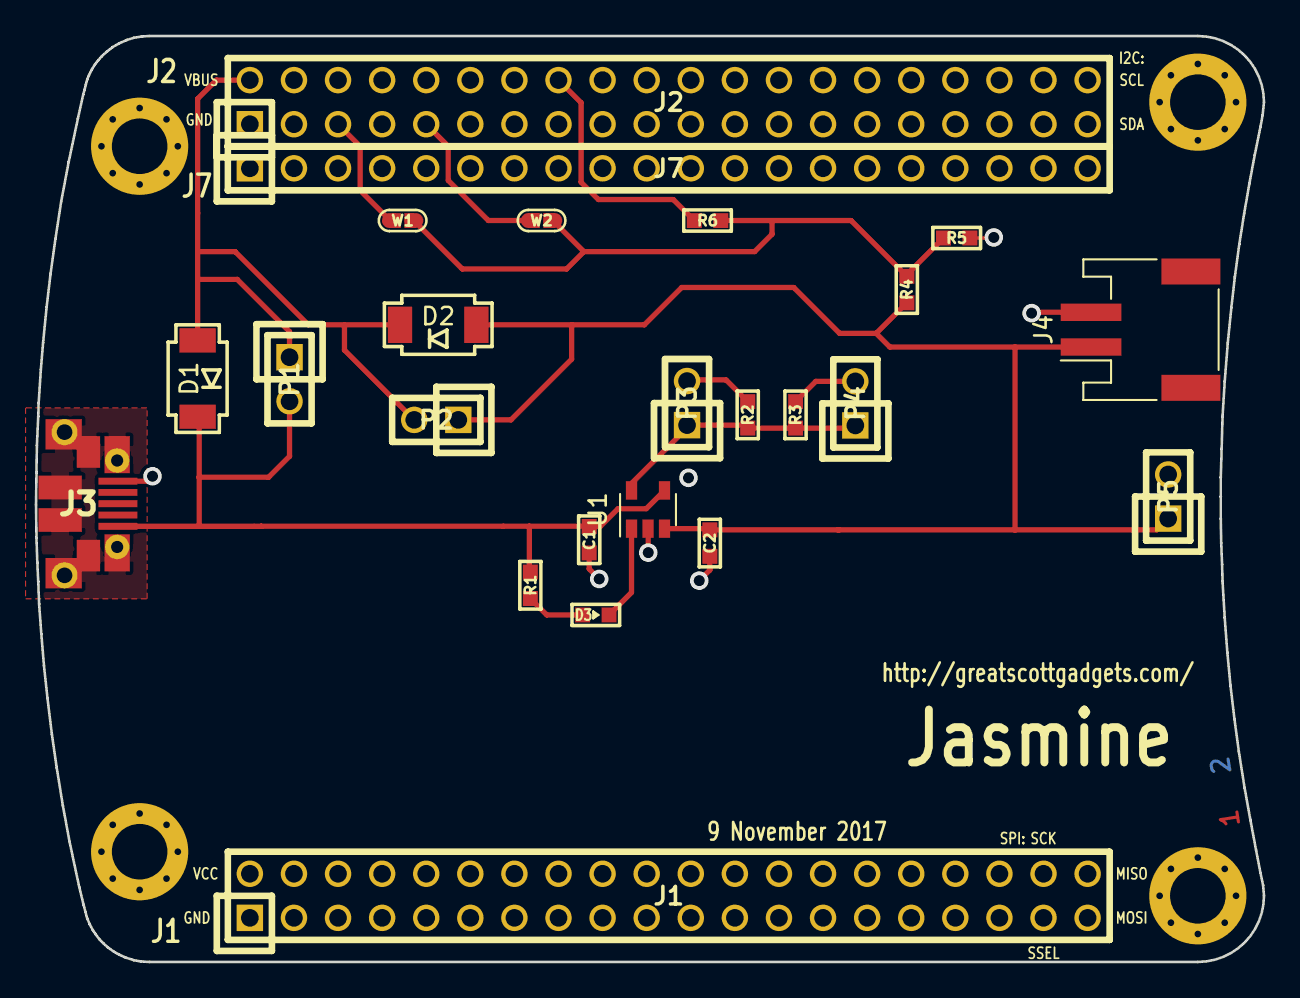
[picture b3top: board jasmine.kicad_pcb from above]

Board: 2 copper layers, 70.7 x 53.3 mm, 28 parts (0 on the bottom side), 11 nets.

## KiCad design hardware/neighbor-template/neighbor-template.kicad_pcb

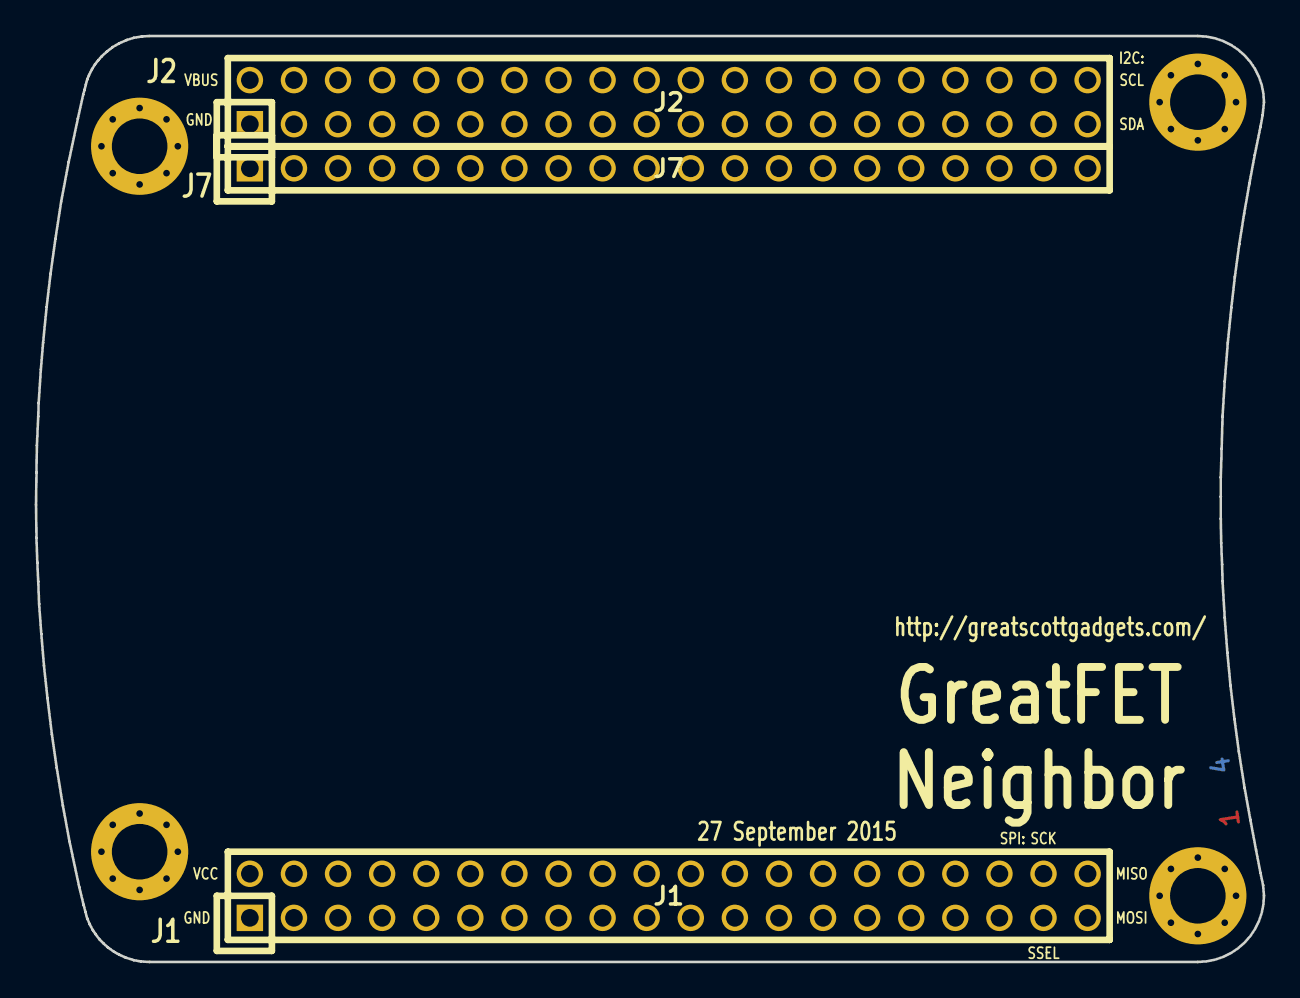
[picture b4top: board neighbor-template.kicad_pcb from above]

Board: 4 copper layers, 70.7 x 53.3 mm, 7 parts (0 on the bottom side), 2 nets, no tracks yet.

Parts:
J1: NEIGHBOR1; HEADER-2x20
J2: NEIGHBOR2; HEADER-2x20
J7: BONUS_ROW; HEADER-1x20
MH1, MH2, MH3, MH4: MOUNTING_HOLE; HOLE126MIL-COPPER

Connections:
GND: J1.1, J2.1, J7.1, J7.10, J7.19, MH1.1, MH2.1, MH3.1, MH4.1
VCC: J1.2, J7.20

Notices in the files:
hardware/azalea/greatfet-one.sch:
Copyright 2015 Michael Ossmann
License: GPL v2
